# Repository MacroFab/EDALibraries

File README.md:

***
### EDALibraries
***
**MacroFab, INC. EDA Part Libraries and usefull tools**

This repository contains the tested and verified footprints for MacroFab's House Part List. Using these footprints will guarantee that the placement of the part is accurate and precise. It also contains useful tools and files to make generating valid manufacturing data easier. Also contains parts for other MacroFab related projects.

The MacroFab style guide for making footprints can be found on the [Part_Style_Guide repository] (https://github.com/MacroFab/MF_Part_Style_Guide). This style guide is designed to reduce problems in the assembly stage of the product.  

***
**License Information**

This project is under the [Creative Commons Attribution 4.0 International License](LICENSE.md). These files are provided with no warranty and should be used at your own risk. 

***

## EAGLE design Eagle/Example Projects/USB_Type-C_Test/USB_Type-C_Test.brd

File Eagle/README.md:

***
### Eagle
***
**Eagle DRC, CAM, Part Libraries, and ULP Scripts**

This directory contains the files needed to generate manufacturing data from Eagle V6.0 and up for MacroFab, INC.

Please see the Eagle documentation at the [knowledge base](https://help.macrofab.com/knowledge/how-to-use-eagle-with-macrofab) on MacroFab, INC. for more information. 

***
**License Information**

This project is under the [Creative Commons Attribution 4.0 International License](LICENSE.md). These files are provided with no warranty and should be used at your own risk. 

***
| Directory | Description |
|---|---|
| CAM | CAM files to generate the needed Gerber Files. | 
| DRU | Design Rule Checks to ensure PCB manufacturability. |
| Libraries | Part libraries for house parts and a few extras. |
| Scripts | Contains useful scripts. |
| ULP | Contains useful ULP scripts. |

***

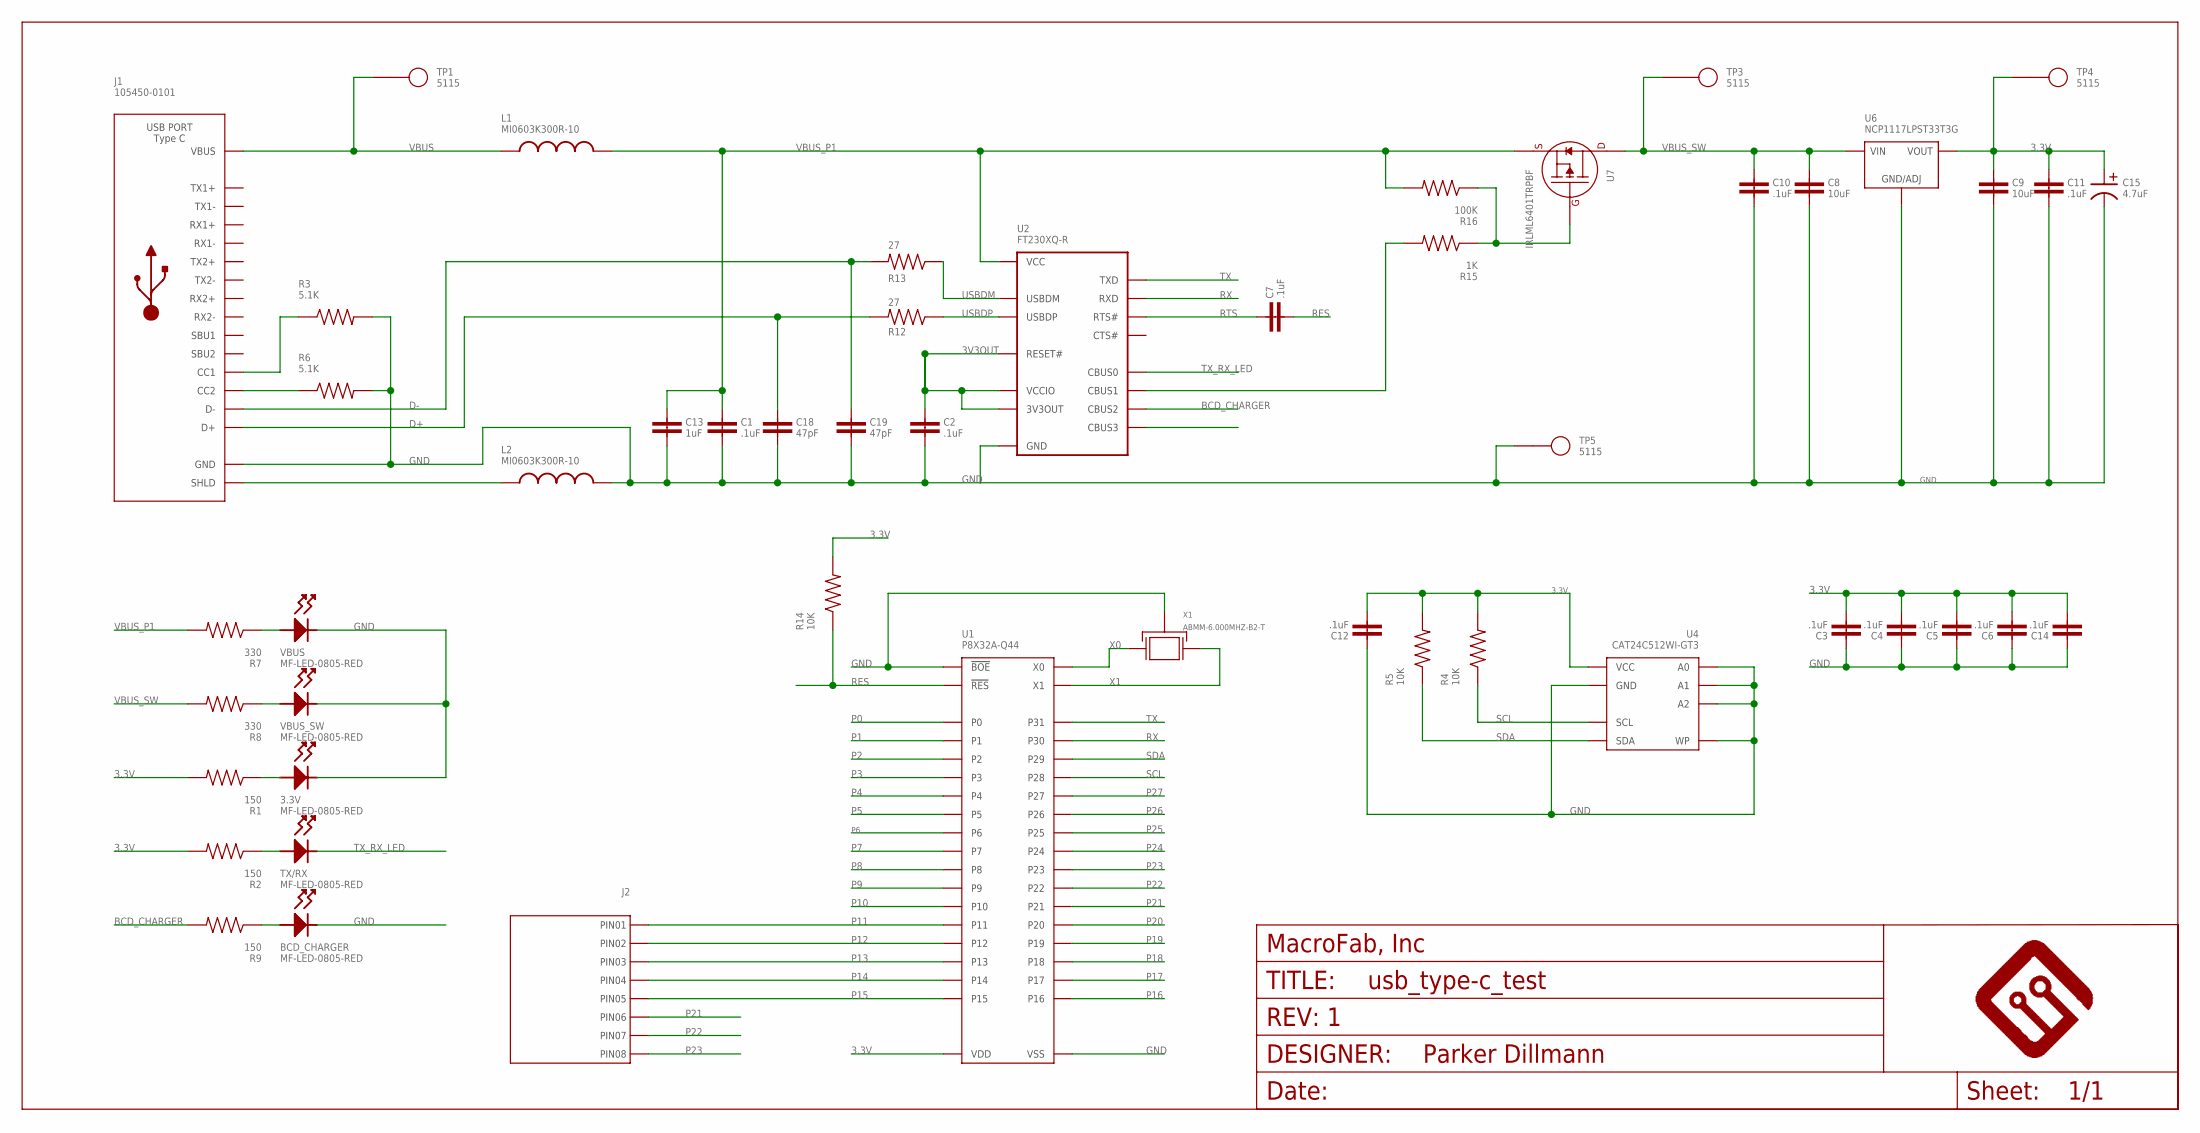
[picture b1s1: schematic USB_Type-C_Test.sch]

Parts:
3.3V: MF-LED-0805-RED; LED_0805
BCD_CHARGER: MF-LED-0805-RED; LED_0805
C1, C2, C3, C4, C5, C6, C7, C10, C11, C12, C14: .1uF; 0603
C8, C9: 10uF; 1206
C13: 1uF; 0603
C15: 4.7uF; 5MM_CAP_SMD
C18, C19: 47pF; 0603
FRAME1: MF_FRAMEDEFAULT; MF_FRAME_DEFAULT
J1: 105450-0101
J2: CON_01X08_2.54MM_PIN_HEADER; 2.54MM_01X08_PIN_HEADER
L1, L2: MI0603K300R-10; 0603
R1, R2, R9: 150; 0603
R3, R6: 5.1K; 0603
R4, R5, R14: 10K; 0603
R7, R8: 330; 0603
R12, R13: 27; 0603
R15: 1K; 0603
R16: 100K; 0603
TP1, TP3, TP4, TP5: 5115; KEYSTONE_5115-5119
TX/RX: MF-LED-0805-RED; LED_0805
U1: P8X32A-Q44; P8X32A_LQFP-44
U2: FT230XQ-R; FT230X_QFN-16
U4: CAT24C512WI-GT3; SOIC-8_W
U6: NCP1117LPST33T3G; SOT-223-3
U7: IRLML6401TRPBF; SOT-23-3
VBUS: MF-LED-0805-RED; LED_0805
VBUS_SW: MF-LED-0805-RED; LED_0805
X1: ABMM-6.000MHZ-B2-T; 7MMX5MM

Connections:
3.3V: C3.2, C4.2, C5.2, C6.2, C9.1, C11.1, C12.2, C14.2, C15.P (POS), R1.2, R2.2, R4.2, R5.2, R14.2, TP4.P$1, U1.8 (VDD), U1.18 (VDD), U1.30 (VDD), U1.40 (VDD), U4.8 (VCC), U6.P$1 (VOUT), U6.P$3 (VOUT)
3V3OUT: C2.1, U2.1 (VCCIO), U2.8 (3V3OUT), U2.9 (RESET#)
BCD_CHARGER: R9.2, U2.5 (CBUS2)
D+: C18.1, J1.A6 (D+), J1.B6 (D+), R12.2
D-: C19.1, J1.A7 (D-), J1.B7 (D-), R13.2
GND: 3.3V.CATHODE, BCD_CHARGER.CATHODE, C1.2, C2.2, C3.1, C4.1, C5.1, C6.1, C8.2, C9.2, C10.2, C11.2, C12.1, C13.2, C14.1, C15.N (NEG), C18.2, C19.2, J1.A1 (GND), J1.A12 (GND), J1.B1 (GND), J1.B12 (GND), L2.2, R3.2, R6.2, TP5.P$1, U1.5 (VSS), U1.6 (!BOE), U1.17 (VSS), U1.27 (VSS), U1.39 (VSS), U2.3 (GND), U2.13 (GND), U2.PAD (GND), U4.1 (A0), U4.2 (A1), U4.3 (A2), U4.4 (GND), U4.7 (WP), U6.P$2 (GND/ADJ), VBUS.CATHODE, VBUS_SW.CATHODE, X1.P$2 (GND), X1.P$4 (GND)
unnamed: 3.3V.ANODE, R1.1
unnamed: R2.1, TX/RX.ANODE
unnamed: BCD_CHARGER.ANODE, R9.1
unnamed: J1.S_T1 (SHLD), J1.S_T2 (SHLD), J1.S_T3 (SHLD), J1.S_T4 (SHLD), L2.1
unnamed: J1.B5 (CC2), R6.1
unnamed: J1.A5 (CC1), R3.1
unnamed: R8.1, VBUS_SW.ANODE
unnamed: R7.1, VBUS.ANODE
unnamed: R15.1, R16.1, U7.1 (GATE)
P0: U1.41 (P0)
P1: U1.42 (P1)
P2: U1.43 (P2)
P3: U1.44 (P3)
P4: U1.1 (P4)
P5: U1.2 (P5)
P6: U1.3 (P6)
P7: U1.4 (P7)
P8: U1.9 (P8)
P9: U1.10 (P9)
P10: U1.11 (P10)
P11: J2.1, U1.12 (P11)
P12: J2.2, U1.13 (P12)
P13: J2.3, U1.14 (P13)
P14: J2.4, U1.15 (P14)
P15: J2.5, U1.16 (P15)
P16: U1.19 (P16)
P17: U1.20 (P17)
P18: U1.21 (P18)
P19: U1.22 (P19)
P20: U1.23 (P20)
P21: J2.6, U1.24 (P21)
P22: J2.7, U1.25 (P22)
P23: J2.8, U1.26 (P23)
P24: U1.31 (P24)
P25: U1.32 (P25)
P26: U1.33 (P26)
P27: U1.34 (P27)
PWREN: R15.2, U2.11 (CBUS1)
RES: C7.2, R14.1, U1.7 (!RES)
RTS: C7.1, U2.16 (RTS#)
RX: U1.37 (P30), U2.2 (RXD)
SCL: R4.1, U1.35 (P28), U4.6 (SCL)
SDA: R5.1, U1.36 (P29), U4.5 (SDA)
TX: U1.38 (P31), U2.15 (TXD)
TX_RX_LED: TX/RX.CATHODE, U2.12 (CBUS0)
USBDM: R13.1, U2.7 (USBDM)
USBDP: R12.1, U2.6 (USBDP)
VBUS: J1.A4 (VBUS), J1.A9 (VBUS), J1.B4 (VBUS), J1.B9 (VBUS), L1.1, TP1.P$1
VBUS_P1: C1.1, C13.1, L1.2, R7.2, R16.2, U2.10 (VCC), U7.2 (SOURCE)
VBUS_SW: C8.1, C10.1, R8.2, TP3.P$1, U6.P$4 (VIN), U7.3 (DRAIN)
X0: U1.29 (X0), X1.P$3 (X1)
X1: U1.28 (X1), X1.P$1 (X0)

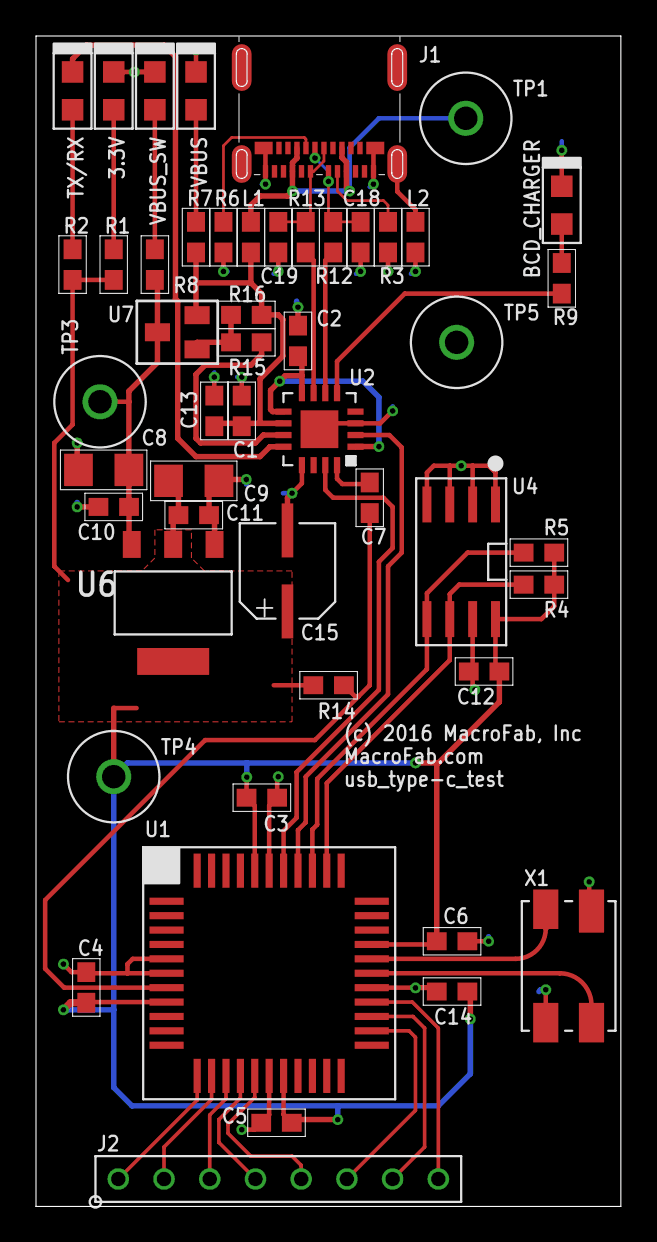
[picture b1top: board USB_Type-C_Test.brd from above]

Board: 2 copper layers, 32.4 x 65.0 mm, 51 parts (0 on the bottom side), 38 nets.

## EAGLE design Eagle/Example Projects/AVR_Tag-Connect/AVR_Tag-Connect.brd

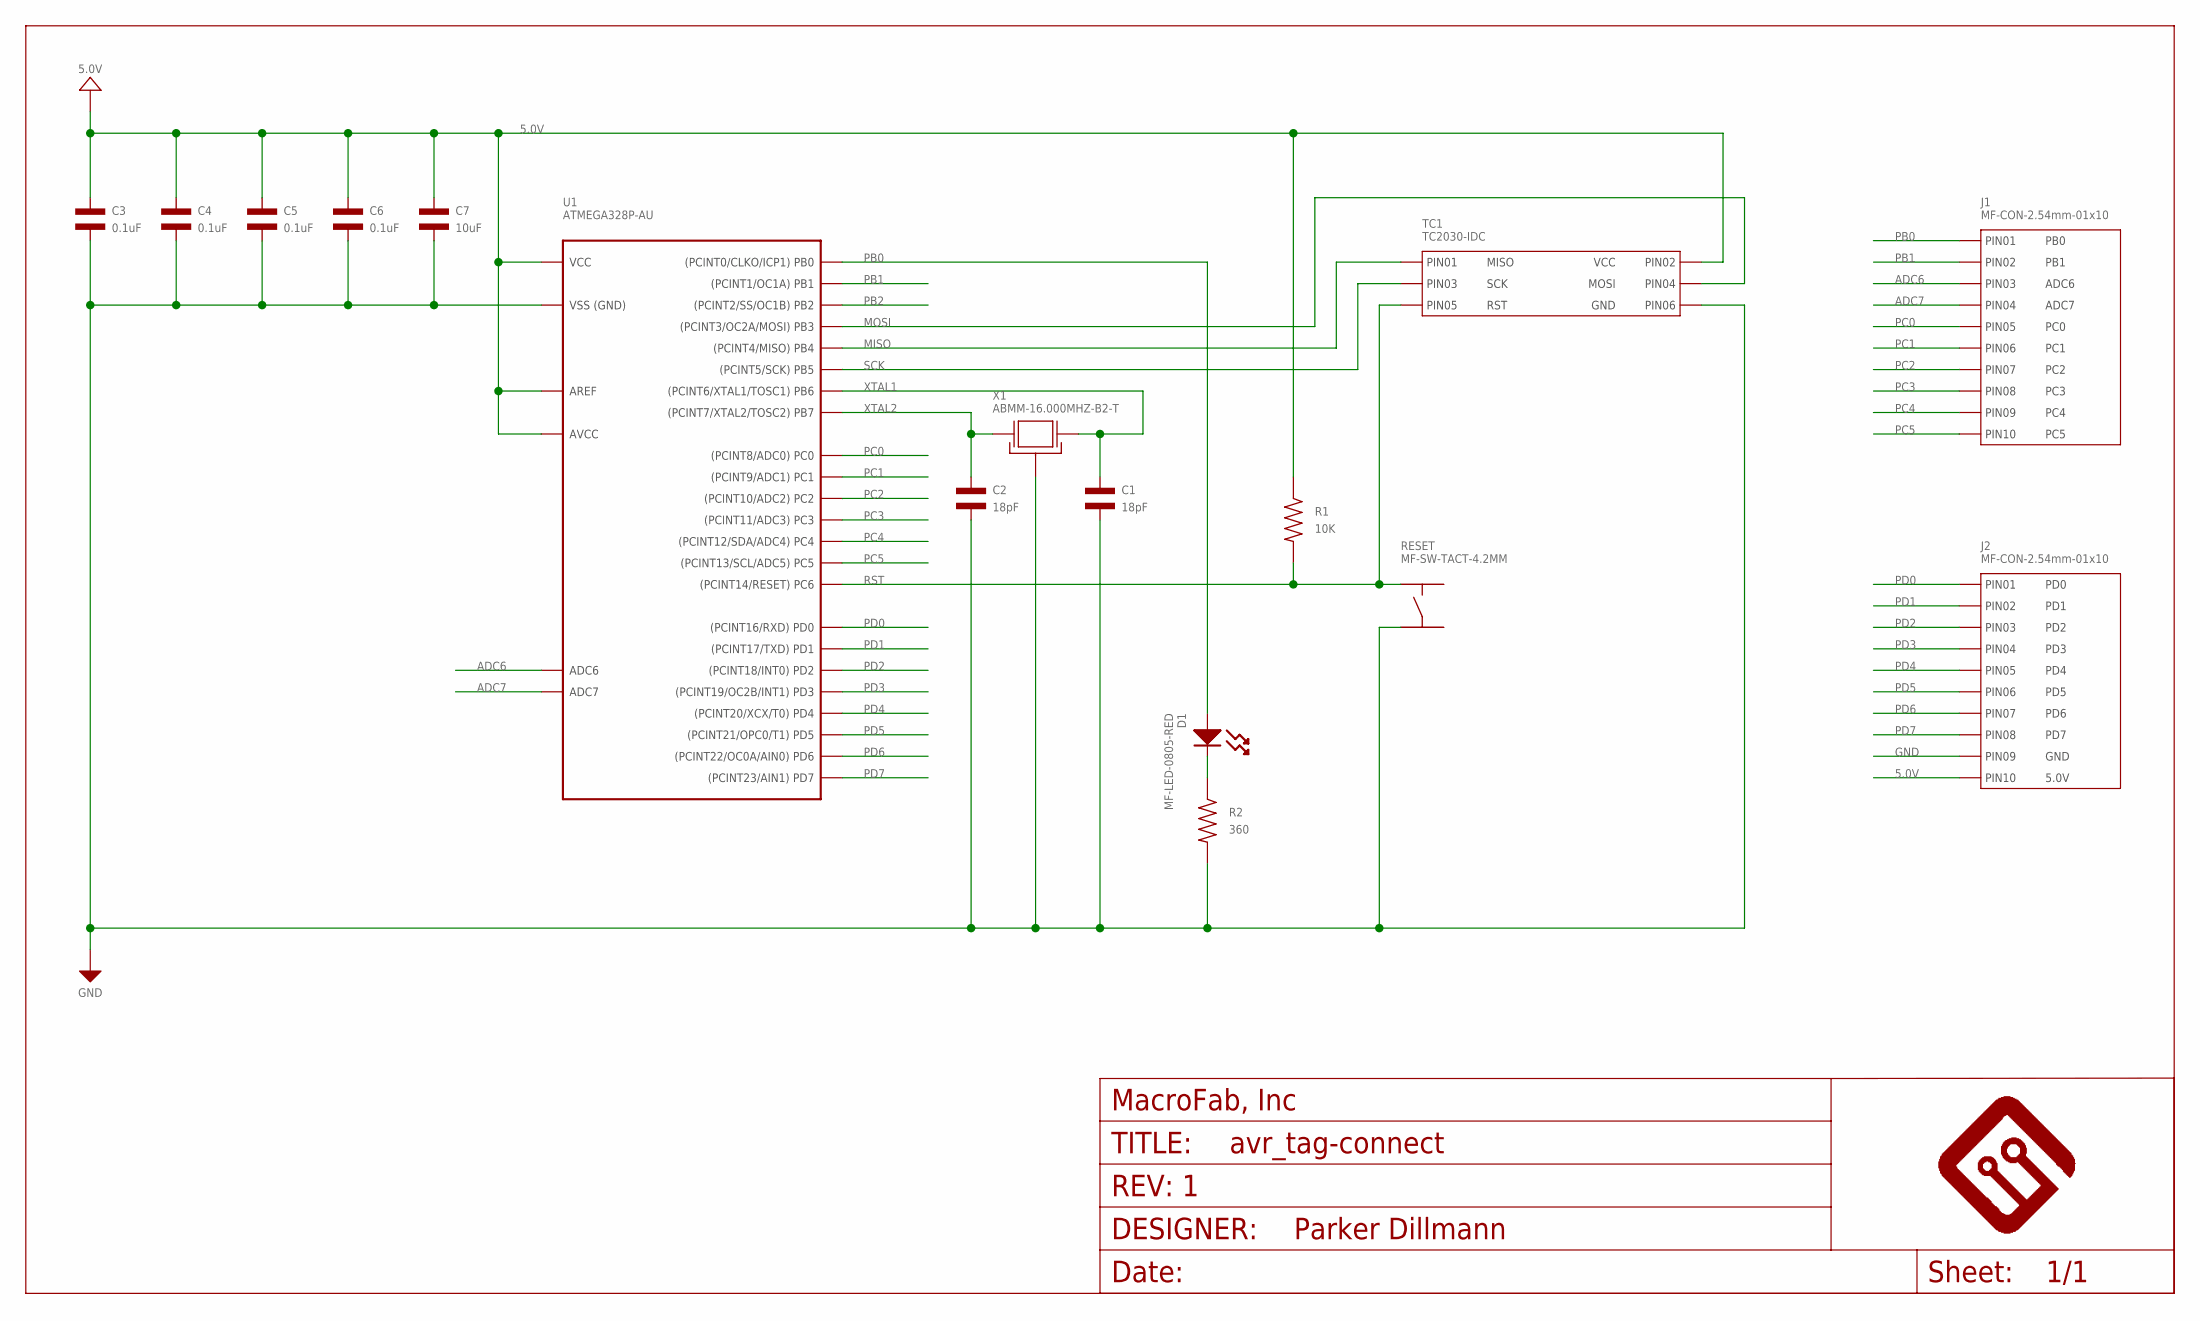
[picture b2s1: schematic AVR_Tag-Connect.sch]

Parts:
C1, C2: 18pF; C0805; MPN 08055A180JAT2A
C3, C4, C5, C6: 0.1uF; C0805; MPN MF-CAP-0805-0.1uF
C7: 10uF; C1206; MPN MF-CAP-1206-10uF
D1: MF-LED-0805-RED; LED0805
FRAME1: MF_FRAMEDEFAULT; MF_FRAME_DEFAULT
J1, J2: MF-CON-2.54mm-01x10; PTH_2.54MM_01X10
R1: 10K; R0805; MPN MF-RES-0805-10K
R2: 360; R0805; MPN MF-RES-0805-360
RESET: MF-SW-TACT-4.2MM; TACT4.2MM
TC1: TC2030-IDC; TC2030-IDC-FP
U1: ATMEGA328P-AU; TQFP32
X1: ABMM-16.000MHZ-B2-T; 7MMX5MM; MPN ABMM-16.000MHZ-B2-T

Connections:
5.0V: C3.P$1, C4.P$1, C5.P$1, C6.P$1, C7.P$1, J2.P$10 (PIN10), R1.P$1, TC1.P$2 (PIN2), U1.P$4 (VCC), U1.P$6 (VCC), U1.P$18 (AVCC), U1.P$20 (AREF)
ADC6: J1.P$3 (PIN3), U1.P$19 (ADC6)
ADC7: J1.P$4 (PIN4), U1.P$22 (ADC7)
GND: C1.P$2, C2.P$2, C3.P$2, C4.P$2, C5.P$2, C6.P$2, C7.P$2, J2.P$9 (PIN9), R2.P$2, RESET.P$3, TC1.P$6 (PIN6), U1.P$3 (GND), U1.P$5 (GND), U1.P$21 (GND), X1.P$2 (GND), X1.P$4 (GND)
MISO: TC1.P$1 (PIN1), U1.P$16 (PB4)
MOSI: TC1.P$4 (PIN4), U1.P$15 (PB3)
unnamed: D1.CATHODE, R2.P$1
PB0: D1.ANODE, J1.P$1 (PIN1), U1.P$12 (PB0)
PB1: J1.P$2 (PIN2), U1.P$13 (PB1)
PB2: U1.P$14 (PB2)
PC0: J1.P$5 (PIN5), U1.P$23 (PC0)
PC1: J1.P$6 (PIN6), U1.P$24 (PC1)
PC2: J1.P$7 (PIN7), U1.P$25 (PC2)
PC3: J1.P$8 (PIN8), U1.P$26 (PC3)
PC4: J1.P$9 (PIN9), U1.P$27 (PC4)
PC5: J1.P$10 (PIN10), U1.P$28 (PC5)
PD0: J2.P$1 (PIN1), U1.P$30 (PD0)
PD1: J2.P$2 (PIN2), U1.P$31 (PD1)
PD2: J2.P$3 (PIN3), U1.P$32 (PD2)
PD3: J2.P$4 (PIN4), U1.P$1 (PD3)
PD4: J2.P$5 (PIN5), U1.P$2 (PD4)
PD5: J2.P$6 (PIN6), U1.P$9 (PD5)
PD6: J2.P$7 (PIN7), U1.P$10 (PD6)
PD7: J2.P$8 (PIN8), U1.P$11 (PD7)
RST: R1.P$2, RESET.P$1, TC1.P$5 (PIN5), U1.P$29 (PC6)
SCK: TC1.P$3 (PIN3), U1.P$17 (PB5)
XTAL1: C1.P$1, U1.P$7 (PB6), X1.P$3 (X1)
XTAL2: C2.P$1, U1.P$8 (PB7), X1.P$1 (X0)

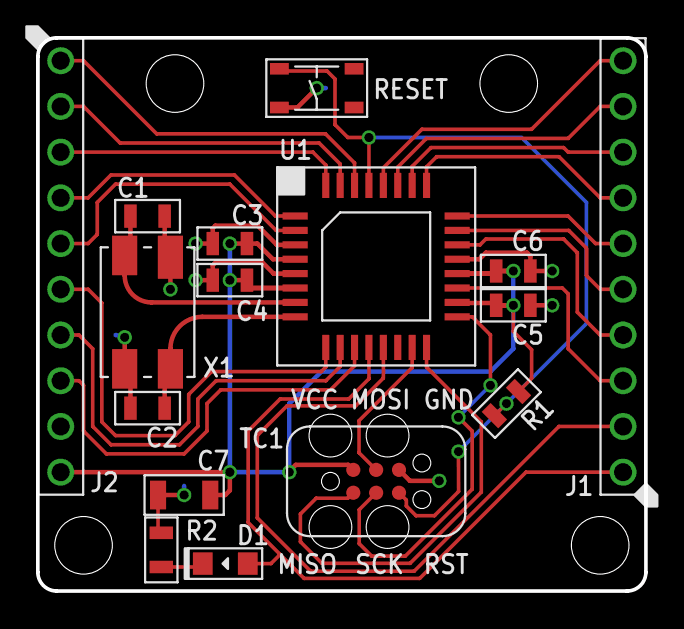
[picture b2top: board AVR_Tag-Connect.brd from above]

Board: 2 copper layers, 33.8 x 30.7 mm, 17 parts (1 on the bottom side), 27 nets.

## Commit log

2014-12-17 Adding Eagle Libraries.
2014-12-17 Finished MF-CON-MICROSDSLOT-RIGHT
    4UCON 15882
2014-12-17 Restructure Eagle Directory to add CAM,DRU,ULP
2014-12-17 More Connectors
    MICROUSB-RIGHT, USB_5PIN, USB_CON_5P, ect...
2014-12-18 Adding 2.54MM Headers
2014-12-19 Finished 2.54MM Headers
2014-12-19 Adding CC-SA license and Readme
2014-12-20 Increased Font on Symbols, MOAR PARTS
2014-12-22 Added MCUs
    ATMEGA328P-AUR
    ATMEGA32U4-AU
    P8X32A-Q44
    CY8C4245PVI-482
    PIC16LF1509T-I/SO
2014-12-22 Added more ICs
    WS2801
    FT232RL
    FT230XS
2014-12-22 Added CH340G
2014-12-22 Added 2 Tact Switches
    6MM, 4.2MM Tact Switches
2014-12-22 Added Power Regulators
    MC33269D-5.0
    LM317MDT
    NCP1117LPST33T3G
    NCP1117LPST50T3G
    NCP1117LPSTADT3G
    TLV70233PDBVR
2014-12-22 Fixed script
2014-12-23 Cant run with .DRL extension set
2014-12-23 Changed Drill file to .XLN
2014-12-24 Added displays, diodes, crystals.
2014-12-26 16026 series display done.
2014-12-29 Added Prefix to TRS_JACK
2015-01-27 Fixed script. Parts with borders error.
    if parts had dimension data (layer20) in them it was ignored.
2015-01-30 Adding example XYRS and PASTE files to public repository.
2015-02-11 Tweaked FT230X symbol
2015-04-14 Fixed ABS issue.
    Pad angle < footprint angle.
2015-05-26 Fixed 6MM Tact footprint.
2015-07-23 Added new 02x03 Connector PTH 2.54MM
2015-07-23 Part for AVX SMD PogoPins
2015-07-24 Fix pogopins
2015-10-21 Fixed Micro USB Connector
    Changed mounting tabs for Micro USB connector from 1.1mm drills to .5mm
    x 1.2mm slots
2015-10-28 Added more Parts
    Added BAT-HLD-001, ABS25 Series Crystals, and PIC16F527-I/ML
2015-11-02 Added new fiducial
2015-11-06 Fixed 01x10 header
2015-12-01 Fixed FTDI part
2015-12-02 Fixed Switch symbol
2015-12-04 Fixing part symbols to bring into style guidelines.
2015-12-14 Fixed PNP Fet Symbol
2015-12-14 Added New 4 Layer DRU and CAM. Added new ULP.
2015-12-14 Added images for Smash_Symbol_Pin_Text.ulp
2015-12-16 Added SI Labs BusyBee MCU EFM8BB1 Series.
2015-12-16 Added zzzzzz sleepy bee
2015-12-17 Added 6/8 layer and updated 2/4 layer
2015-12-17 New ReadMEs!
2016-02-03 Added exceptions for mirror parts and better error codes
2016-02-12 Libraries for Diptrace
    Added libraries to match the Eagle
2016-02-17 tweaked USB shield connections.
2016-03-02 Updated example XYRS file to include populate/MPN columns.
2016-03-15 Added chassis ground symbol
2016-03-18 Generate XLN without 10x scale
    The "EXCELLON" processor generates drill files with 10x normal scale. Need 2.4 file.
2016-03-18 Generate 2.4 Excellon files to avoid 10x scale
2016-03-18 Generate Excellon_24 format to avoid 10x scale
2016-03-18 Generate Excellon_24 format files to avoid 10x scale
2016-03-30 Added Eagle V6 and V7 Cam Files.
    Difference is V6 runs EXCELLON drills and V7 runs EXCELLON_24 drills.
2016-04-25 added TPS7B69 part
2016-05-24 Fixed offset issue with Eagle ULP
2016-05-24 fixed for realz. had to take X-Y from center of line.
2016-06-07 Fixed mirrored angle issues.
2016-06-14 Updated MICROUSB-RIGHT to Milling 46 for DRC.
2016-06-21 Fixed ULP bug with acute arcs.
2016-06-21 Added paste file back in :X
2016-06-27 added ECX-31B footprint for MacroWatch V2
2016-07-22 Fixed microusb. Dunno why those lines where removed.
2016-07-25 Added MPN and Populate Attribute checks.
    Fixed X center and Y center calculations for non symmetrical parts with
    large offset pads (EX: D2PAK) .
2016-07-25 Adding DRU checks
    These are all the different DRCs that MacroFab supports.
2016-07-25 Updated the help file location.
2016-08-02 Big update on the Part Libraries in Eagle.
    Updated all the footprints to fix upload part matching for houseparts.
    Each part now has Housepart, MPN, Populate, URL, and Value attribute.
2016-08-02 Rewrote the rotation SMT and part center finding.
    Part sizes are now calculated by the footprint library stored in the
    .BRD file. Part centering is now calculated off of the pads center and
    if the footprint has any offset.
2016-08-08 Fixed pogo pin footprint labeling
    LABEL00 to LABEL01
2016-08-09 Adding AVR_Tag-Connect Eagle example.
2016-08-09 Adding USB Type C Test Board to Eagle Samples.
2016-08-10 Tweaked MF Frame.
2016-08-10 Fixed rotation on SOT-223-3
2016-08-10 Adding Eagle Scripts
    scripts to be used for set-all-devices-attribute.ulp
2016-08-10 updating readme to latest standard.
2016-08-10 Moving Eagle Example Projects to Macro_Articles.
2016-08-12 Added Kicad footprint library
2016-08-15 Adding SILabs2TC tagconnect.
2016-08-15 Added Diptrace template and rule files and cleaned up the directories
2016-08-15 Fixed L1210 package discription. Thanks MC!
2016-08-17 Removed paste from TagConnect footprints
2016-08-17 Fixed paste/soldermask on some PTH pads
2016-08-25 Added schematic symbols
2016-08-30 Fixed polygon inside footprints.
2016-09-13 Updating SiLabs TagConnect to have PinShare.
2016-09-28 Removing depricated parts.
    Removed MF-LED-5060-RGB and replaced it with MF-LED-3228-RGB
2016-09-30 added STM32 SWD2TC footprint
2016-10-21 Revert MicroUSB routes to Milling.
    Milling layer in Eagle does not push back on inner layers in new version
    of Eagle.
2017-01-25 Changed copyright from 2016 to 2017
2017-02-08 Update pins to common pin format to support REPLACE
    Now you can REPLACE most components from most other libraries with the components in these libraries as pin names will properly match (eg, adjusted "P$1" to "1")
2017-02-08 Removed VALUE attribute to prevent value overwriting during REPLACE
    When you REPLACE a component with one of these packages, the technology had an attribute named 'VALUE' that removed any existing value you had in place -- those empty values are now gone allowing you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
2017-02-15 Added 2 new ULPs.
2017-04-25 Opened each library in KiCad 4.0.6 and re-saved to clean up file format
2017-04-25 Clean up text placement in the SD Card component
2017-04-25 Add .gitignore to ignore the KiCad backup files
2017-04-25 Move PIN01 label to be consistent with the other connectors
2017-04-25 Move PIN01 label on the POGO pin to be consistent with the other connectors
2017-04-26 Updates to the single line connector schematics and footprints
    - use pin labels instead of added text fields
    - use pin number values instead of eagle style strings
    - use fields for labels on schematics
    - update footprints to use pin number values
2017-04-28 Move footprint field so that it doesn't overlap
2017-04-28 Clean up all the 02x03 connector schematics and footprints
2017-04-28 Clean up all the 02x05 connector schematics and footprints
2017-04-28 Clean up the rest of the connectors
2017-04-28 Fixed MPN for MF-REG-SOT235-3.3V-300mA
2017-04-29 Bugfix for Issue #5: KiCad component value text on wrong layer
    (https://github.com/MacroFab/EDALibraries/issues/5)
    - Updated all component values to be on F.Fab layer by default
2017-04-30 Change Eagle style pin names for pins in all schematics and footprints
2017-04-30 Remove duplicated fiducial component from wrong library
2017-05-01 Add a space to README titles to get markdown to show properly
2017-05-03 Many updates to layouts to make them more KiCad style
    - Made pin names and numbers visible instead of text labels
    - Moved labels out of the way of pins
    - Changed 4 polyline boxes into normal rectangles
    - Updated some pin locations for better labels and flow
2017-09-22 adding BOM spread sheet example
2017-09-22 OrCAD extract file
2017-09-22 Impedance control example gerber
2017-10-31 Changing the license from CC BY SA to CC BY
2017-12-06 Removed extra pins from TC2050 footprints. These will show up properly in cvpcb now when filtering on pin count.
    XOXO AND!XOR
2018-07-05 Changed copyright from 2017 to 2018
2018-07-25 Changed footprint variable to footprintname
    In Eagle 9.1, footprint became a reserved word in the ULP language.
2018-08-20 Removed Value Attribute From Libraries
2018-08-20 Fixed EFM8BB10F(2/4/8)G-A-QFN20
2018-12-18 Updating DRC rules for new Standard MFG rules
2019-01-18 Adding Design blocks for Eagle: USB Type C FT230X
2019-02-21 Fixed IP4234CZ6 in Design Blocks
2019-07-17 Updating Type-C design blocks
2019-12-09 Update USB_Type-C_USB_2_0.dbl
    Fixing a couple issues with silkscreen
2021-08-19 updated MF frame for 2021
2021-10-20 First version of Altium DRC and Stackup files for MF
2022-02-22 Add Altium gitignore
2022-02-22 Add export BOM template
2022-02-22 Add capacitor template component
2022-02-25 ﻿Add Macrofab house capacitors
2022-02-25 Add template LibPkg
2022-02-25 Add Macrofab connectors
2022-02-26 Add Macrofab Diodes
2022-02-28 Add Macrofab transistors
2022-02-28 Add MF-IC-SOP14-WS2801 LED Driver
2022-02-28 Add MF-IND-1210-10uH
2022-02-28 Add Macrofab LEDs
2022-02-28 Clean up template
2022-03-01 Add Macrofab power IC
2022-03-01 Add Macrofab resistors
2022-03-01 Add Macrofab switches
2022-03-02 ﻿Add basic ODB++ outjob.
2024-02-28 updating copyright year
2024-02-29 added RP2040_QFN

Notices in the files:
parts and their libraries:
MF_Aesthetics: (c) 2016 MacroFab, Inc
